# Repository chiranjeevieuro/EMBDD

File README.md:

# EMBDD
All template projects that are fully functional will be added into this repo.
- Program used: [KiCAD](https://www.kicad.org/)
---
1. LT8602, 4 channel powersupply board with LED indication (https://github.com/silardg/EMBDD/tree/main/4channelPowerSupply)
2. Servo controller, containing an STM32, motor driver, CAN Bus driver in a very small package (https://github.com/silardg/EMBDD/tree/main/servoController)
---
[My LinkedIn](https://www.linkedin.com/in/silard-gal/)

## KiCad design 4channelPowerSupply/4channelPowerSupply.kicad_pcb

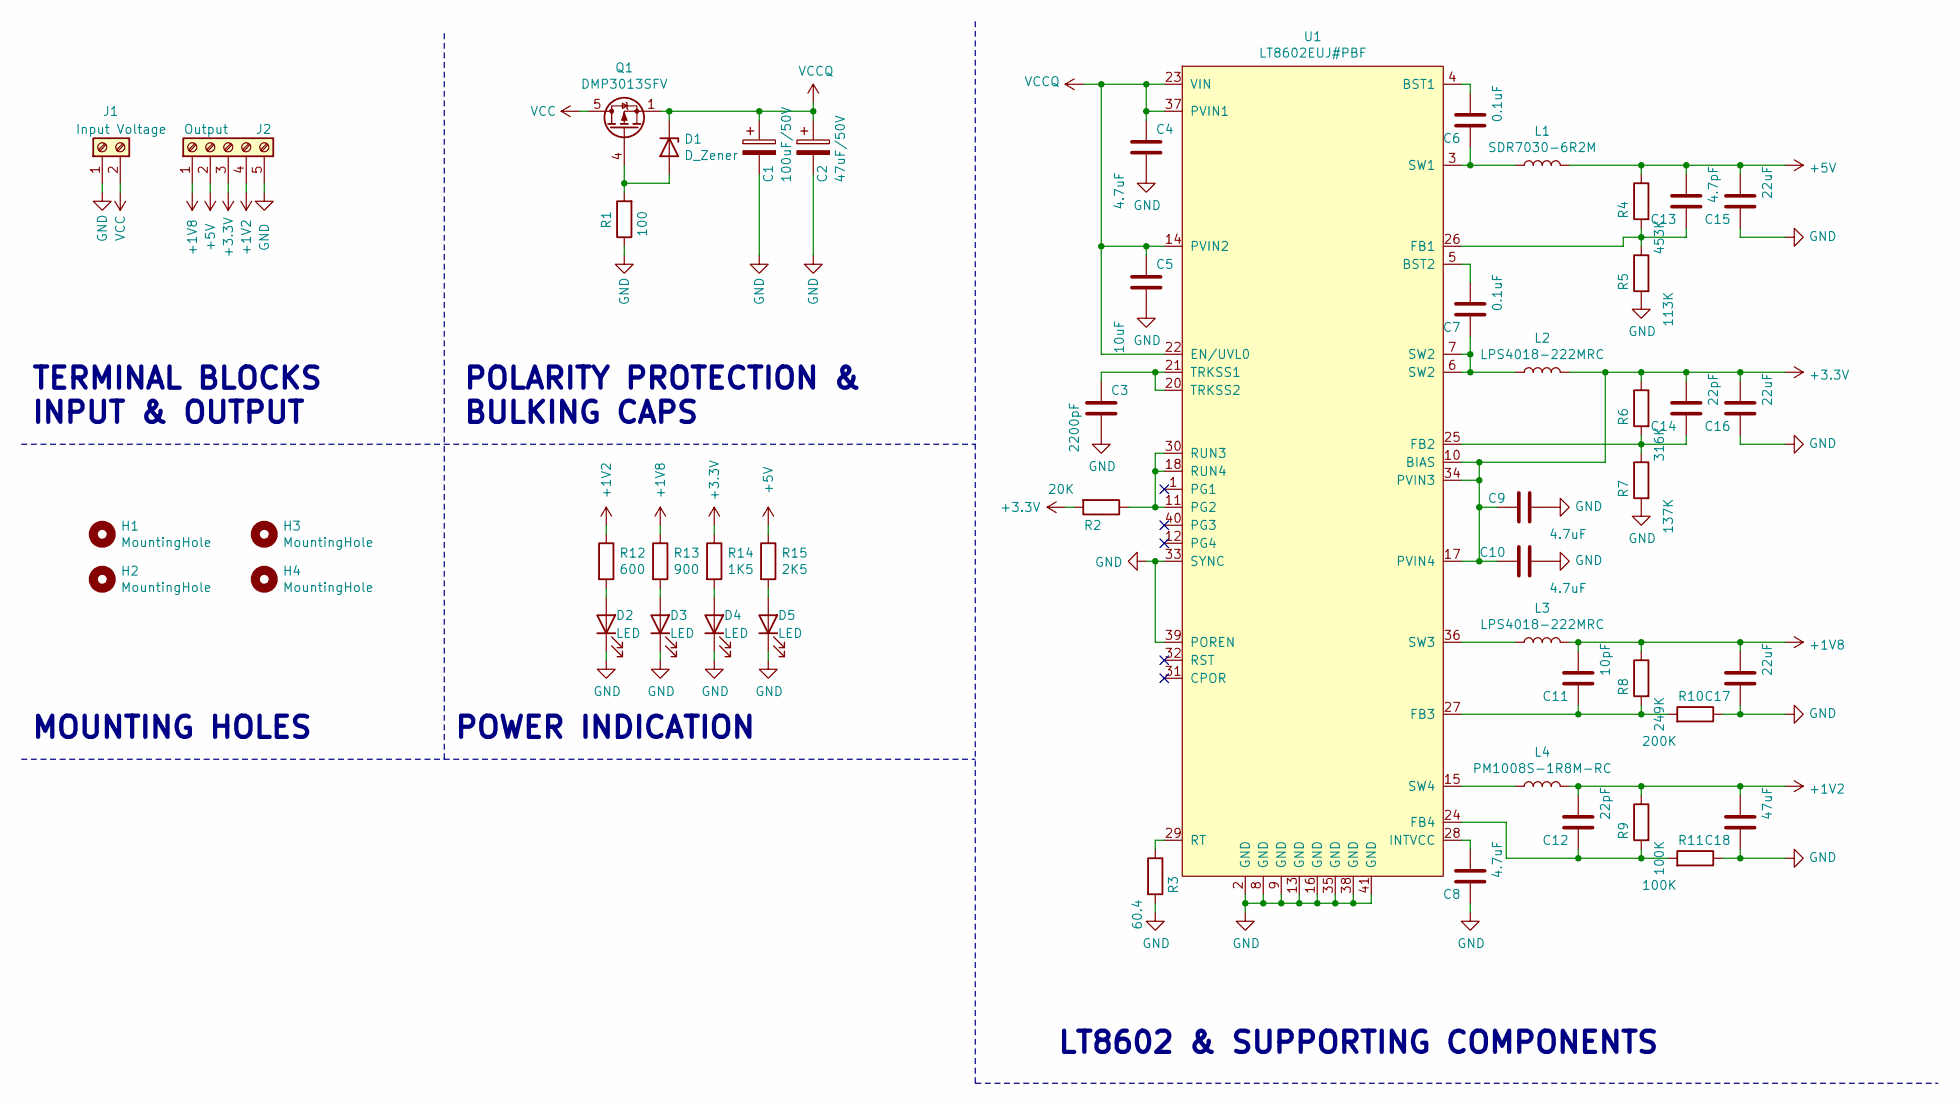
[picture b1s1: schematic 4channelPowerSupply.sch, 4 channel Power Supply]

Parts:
C1: 100uF/50V; C_Elec_6.3x5.4
C2: 47uF/50V; C_Elec_6.3x5.4
C3: 2200pF; C_0603_1608Metric
C4, C8, C9, C10: 4.7uF; C_0603_1608Metric
C5: 10uF; C_0603_1608Metric
C6, C7: 0.1uF; C_0603_1608Metric
C11: 10pF; C_0603_1608Metric
C12, C14: 22pF; C_0603_1608Metric
C13: 4.7pF; C_0603_1608Metric
C15, C16, C17: 22uF; C_0603_1608Metric
C18: 47uF; C_0603_1608Metric
D1: D_Zener; D_0603_1608Metric
D2, D3, D4, D5: LED; LED_0603_1608Metric
H1, H2, H3, H4: MountingHole; MountingHole_3.2mm_M3_Pad_Via
J1: Input Voltage; TerminalBlock_Phoenix_MKDS-1,5-2_1x02_P5.00mm_Horizontal
J2: Output; TerminalBlock_Phoenix_MKDS-1,5-5-5.08_1x05_P5.08mm_Horizont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
L1: SDR7030-6R2M; L_Bourns_SRP7028A_7.3x6.6mm
L2, L3: LPS4018-222MRC; L_Coilcraft_XxL4020
L4: PM1008S-1R8M-RC; L_1008_2520Metric_Pad1.43x2.20mm_HandSolder
Q1: DMP3013SFV; Diodes_PowerDI3333-8
R1: 100; R_0603_1608Metric
R2: 20K; R_0603_1608Metric
R3: 60.4; R_0603_1608Metric
R4: 453K; R_0603_1608Metric
R5: 113K; R_0603_1608Metric
R6: 316K; R_0603_1608Metric
R7: 137K; R_0603_1608Metric
R8: 249K; R_0603_1608Metric
R9, R11: 100K; R_0603_1608Metric
R10: 200K; R_0603_1608Metric
R12: 600; R_0603_1608Metric
R13: 900; R_0603_1608Metric
R14: 1K5; R_0603_1608Metric
R15: 2K5; R_0603_1608Metric
U1: LT8602EUJ#PBF; QFN-40-1EP_6x6mm_P0.5mm_EP4.6x4.6mm_ThermalVias

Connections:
+1V2: C12.2, C18.2, J2.4, L4.2, R9.1, R12.1
+1V8: C11.2, C17.2, J2.1, L3.2, R8.1, R13.1
+3V3: C9.1, C10.1, C14.2, C16.2, J2.3, L2.2, R2.2, R6.1, R14.1, U1.10 (BIAS), U1.17 (PVIN4), U1.34 (PVIN3)
+5V: C13.2, C15.2, J2.2, L1.2, R4.1, R15.1
GND: C1.2, C2.2, C3.2, C4.2, C5.2, C8.1, C9.2, C10.2, C15.1, C16.1, C17.1, C18.1, D2.1 (K), D3.1 (K), D4.1 (K), D5.1 (K), J1.1, J2.5, R1.1, R3.2, R5.2, R7.2, R10.1, R11.1, U1.2 (GND), U1.8 (GND), U1.9 (GND), U1.13 (GND), U1.16 (GND), U1.33 (SYNC), U1.35 (GND), U1.38 (GND), U1.39 (POREN), U1.41 (GND)
unnamed: C3.1, U1.20 (TRKSS2), U1.21 (TRKSS1)
unnamed: C6.1, L1.1, U1.3 (SW1)
unnamed: C6.2, U1.4 (BST1)
unnamed: C7.1, L2.1, U1.6 (SW2), U1.7 (SW2)
unnamed: C7.2, U1.5 (BST2)
unnamed: C8.2, U1.28 (INTVCC)
unnamed: C11.1, R8.2, R10.2, U1.27 (FB3)
unnamed: C12.1, R9.2, R11.2, U1.24 (FB4)
unnamed: C13.1, R4.2, R5.1, U1.26 (FB1)
unnamed: C14.1, R6.2, R7.1, U1.25 (FB2)
unnamed: D1.2 (A), Q1.4 (G), R1.2
unnamed: D2.2 (A), R12.2
unnamed: D3.2 (A), R13.2
unnamed: D4.2 (A), R14.2
unnamed: D5.2 (A), R15.2
unnamed: L3.1, U1.36 (SW3)
unnamed: L4.1, U1.15 (SW4)
unnamed: R2.1, U1.11 (PG2), U1.18 (RUN4), U1.30 (RUN3)
unnamed: R3.1, U1.29 (RT)
VCC: J1.2, Q1.5 (D)
VCCQ: C1.1, C2.1, C4.1, C5.1, D1.1 (K), Q1.1 (S), Q1.2 (S), Q1.3 (S), U1.14 (PVIN2), U1.22 (EN/UVL0), U1.23 (VIN), U1.37 (PVIN1)

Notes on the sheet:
TERMINAL BLOCKS INPUT & OUTPUT
POLARITY PROTECTION & BULKING CAPS
LT8602 & SUPPORTING COMPONENTS
MOUNTING HOLES
POWER INDICATION

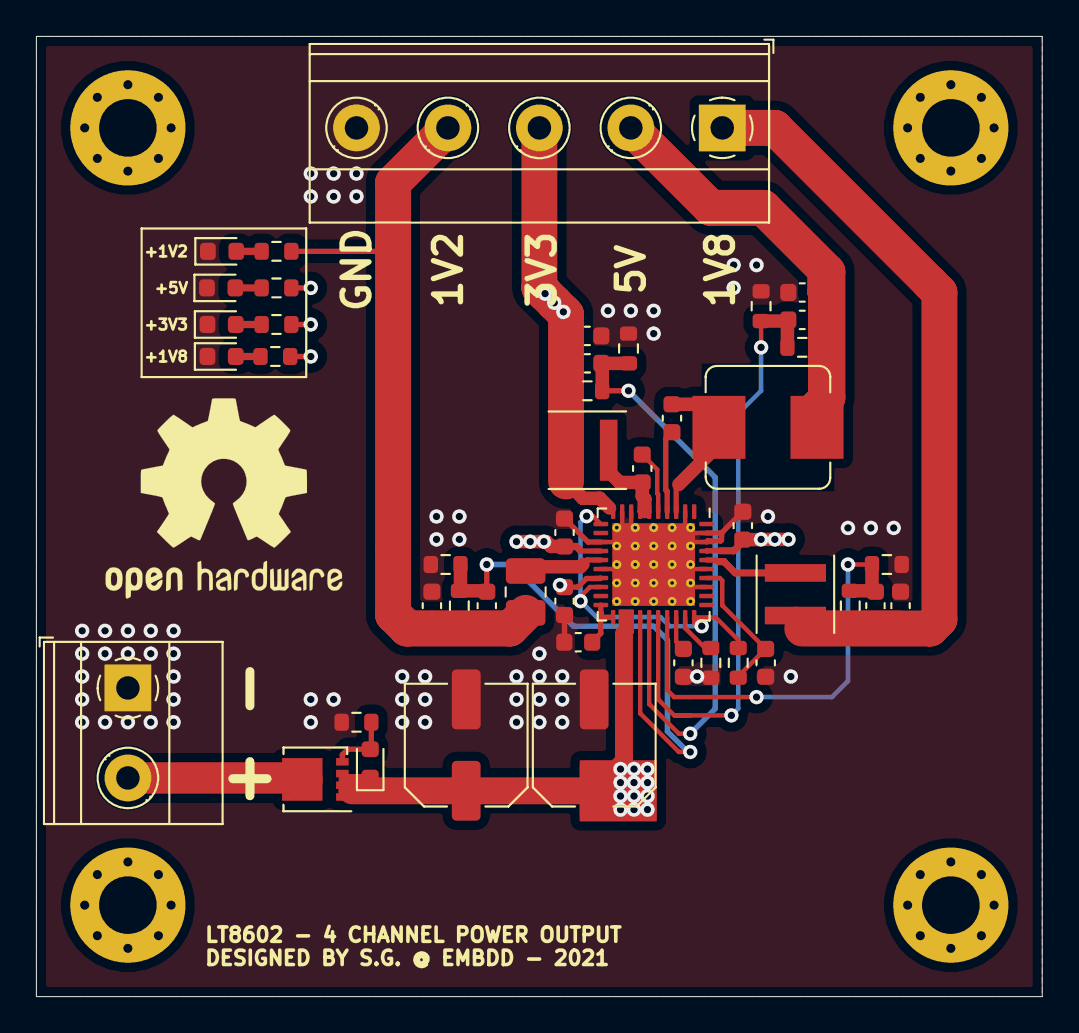
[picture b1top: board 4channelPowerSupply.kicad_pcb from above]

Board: 4 copper layers, 55.9 x 53.3 mm, 50 parts (0 on the bottom side), 26 nets.

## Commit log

2021-06-02 Added new project
2021-06-02 Added main components
2021-06-02 Net generated and added all components
2021-06-02 Added indication
2021-06-02 Footprint for zener
2021-06-02 Removed label from each component, starting pcb design...:
2021-06-05 Finished first project, yay
2021-06-05 Touchup
2021-06-13 Added servController project with schematic
2021-06-13 Servocontroller
